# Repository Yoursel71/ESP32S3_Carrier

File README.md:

# ESP32-S3 Carrier Board (KiCad 10)

A 2-layer handheld carrier PCB for the ESP32-S3-DevKitC-1 (N16R8). Every module plugs into 2.54 mm female header sockets; the board itself only carries the sockets, buttons, power circuitry, IR parts and passives.

| | |
|---|---|
| Board | 116 × 200 mm, 2 layers, 1.6 mm FR4, R4 rounded corners, 4× M3 holes (5 mm from the edges) |
| Modules | CC1101 433 MHz (top centre), 2× NRF24L01+PA+LNA, PN532 V3 (I2C), RDM6300 125 kHz, Si5351 clock generator (3× SMA), Catalex microSD, 1.3" SH1106 I2C OLED |
| Power | 18650 Li-ion via JST-PH, TP4056 charger (protected), main power switch, MT3608 boost → 5 V, AMS1117 → 3.3 V, battery level on IO3 |
| On board | 3× IR LED (940 nm) + VS1838B receiver, passive buzzer, 6 buttons (D-pad + OK + BACK), module power switch with soft-start |
| ERC | **0 errors, 0 warnings** (`output/ERC_report.rpt`) |
| DRC | **0 violations, 0 unconnected pads, schematic ↔ PCB in sync** (`--schematic-parity --severity-all`, `output/DRC_report.rpt`) |
| Routing | Freerouting 2.5.0, 100 % routed; GND pour on both layers + 305 stitching vias |
| Tracks | signal 0.25 mm, power 0.6 mm, GND 0.5 mm, minimum 0.20 mm; clearance 0.20–0.25 mm; vias 0.6/0.3 and 0.8/0.4 mm |

## Files

| File | Contents |
|---|---|
| `ESP32S3_Carrier.kicad_pro / .kicad_sch / .kicad_pcb` | KiCad 10 project |
| `Carrier.kicad_sym`, `Carrier.pretty/` | Project symbols and module socket footprints (module body on Fab + courtyard) |
| `output/board_explorer.html` | **Interactive 3D board explorer**: open it in a browser, toggle layers, pull them apart, click a track to light up its whole net and list the connected pins |
| `output/render_top.png`, `render_perspective.png`, `render_bottom.png` | 3D renders |
| `output/assembly_1to1.pdf` | **1:1 assembly check drawing** (A4, unscaled, 50 mm check bar) |
| `output/copper_layers_1to1.pdf` | Top and bottom copper, 1:1 |
| `output/schematic.pdf` | Schematic |
| `output/ERC_report.rpt`, `output/DRC_report.rpt` | Check reports |
| `output/gerbers_ESP32S3_Carrier.zip` | Fabrication files (Gerber + Excellon) |
| `output/BOM.csv` | Bill of materials |
| `scripts/` | Regenerates everything from one source file (`design.py`) |

## Pin map (ESP32-S3)

| Function | GPIO |
|---|---|
| I2C SDA / SCL (OLED 0x3C, PN532 0x24, Si5351 0x60) | IO8 / IO18 (4.7k pull-ups to +3V3_MOD) |
| SPI MOSI / SCK / MISO (CC1101, microSD, 2× NRF24) | IO11 / IO12 / IO13 |
| CC1101 CS / GDO0 / GDO2 | IO10 / IO9 / IO42 |
| microSD CS | IO14 |
| NRF24 #1 CE / CSN / IRQ | IO4 / IO5 / IO21 |
| NRF24 #2 CE / CSN / IRQ | IO6 / IO7 / IO48 |
| IR receiver VS1838B | IO1 |
| IR transmitter (Q1 PN2222A, 220 Ω base, 3 LEDs) | IO2 |
| Passive buzzer (Q2 driver) | IO47 |
| Buttons UP / DOWN / LEFT / RIGHT / OK / BACK (pull to GND) | IO15 / IO16 / IO38 / IO39 / IO40 / IO41 |
| RDM6300 TX (5 V → 3.4 V divider) | IO17 |
| Battery voltage (100k/100k divider, read × 2) | IO3 (ADC) |
| Unused | 0, 19, 20, 35–37, 45, 46, TX/RX, RST |

Enable the internal pull-ups for the buttons. On DevKitC-1 v1.1, IO38 also drives the on-board RGB LED, so the button works but the RGB LED cannot be used at the same time. GDO2 and the two NRF24 IRQ lines are optional; firmware may ignore them.

## Power

```
18650 ─ J10 ─ TP4056 (charges from its own USB, DW01 protection) ─ OUT ─ SW8 main switch (Q4 P-MOSFET)
      ─ MT3608 boost (set to 5.3 V) ─ D5 SS34 ─► +5V
USB → DevKit 5V pin ─────────────────────────────────────────► +5V   (diode-OR'ed with the battery path)

+5V ──[Q3 AO3401A, soft-start]── +5V_MOD ──┬─ microSD (5 V), RDM6300 (5 V), 3× IR LED, buzzer
                     SW7 slide switch drives Q3's gate          └─ U2 AMS1117-3.3 → +3V3_MOD → CC1101, 2× NRF24, PN532, OLED, Si5351, VS1838B
```

- **SW8 (MAIN PWR):** connects the battery to the boost converter. Off = no battery drain (the battery-level divider sits after the switch).
- **Charging:** plug USB into the TP4056 module at the left edge. The protected module's OUT- is the board ground; B- only goes to the cell.
- **Battery + USB together:** the DevKit USB and the boosted battery both feed +5V through diodes, so you can program with the battery connected.
- **Set the MT3608 to 5.3 V** with its trimmer before plugging anything in; after the SS34 drop the rail sits near 4.9 V.
- **SW7 OFF:** the ESP32 keeps running, every module is unpowered.
- **Soft-start:** R16 (100k) + C16 (100 nF gate-drain) ramp +5V_MOD in about 20 ms. Without it, switching ~900 µF of module capacitance on at once would pull the DevKit's 5 V rail down and reset the ESP32.
- The modules' 3.3 V comes from a separate AMS1117, not from the DevKit's 3V3 pin (two PA+LNA radios + PN532 + Wi-Fi would overload the DevKit regulator).
- Decoupling: 100 nF at every module's VCC; an extra 100 µF at the CC1101 and both NRF24s; 470 µF bulk on +3V3_MOD; a 100 µF reservoir next to the IR LEDs.
- Peak current can approach 1 A, so use a decent USB port or charger. Under load +5V_MOD may sit near 4.5 V; if +3V3_MOD sags, replace U2 with a low-dropout SOT-223 regulator that has the same pin-out (1 GND, 2 VOUT, 3 VIN).
- While SW7 is off, firmware should not drive module pins (CS etc.) high, otherwise the modules get back-powered through their I/O pins.

## Rev 1.2

- 18650 battery power: JST-PH battery connector, TP4056 protected charger, main power switch (P-MOSFET), MT3608 5 V boost, SS34 diode-OR with USB.
- Battery voltage measurement on IO3.
- Board grows to 116 × 200 mm; the lower half (DevKit, buttons, Si5351) moved down 30 mm.
- TP4056 and MT3608 are mounted flat and tied to the board with pin legs or short wires (their pad layout varies between clones; check yours against the 1:1 sheet).

## Design review (rev 1.1)

All connections were re-checked pin by pin against the module pin-outs (`scripts/netcheck.py` compares the schematic netlist with `design.py`). Changes from rev 1.0:

1. **Inrush fix (bug):** module power is now soft-started (see above).
2. **IR receiver:** rotated 180° so the lens faces the board edge (it faced inwards); added an R11/C11 (100 Ω / 100 nF) supply filter as recommended in the VS1838B datasheet.
3. **IR transmitter:** three IR LEDs, each with its own 47 Ω resistor (~67 mA each, ~0.2 A total through Q1), plus a 100 µF local reservoir. Drive IO2 only with the modulated 38 kHz carrier and never hold it high: the LEDs and resistors are sized for pulsed use.
4. **SPI chip selects:** 10k pull-ups (R12–R15) keep every SPI device deselected while the ESP32 boots.
5. **CC1101 moved to the centre** of the top edge; the NRF24s sit at the corners with the IR parts in between.
6. **Si5351A added** (7-pin module) on the shared I2C bus, bottom right, with its three SMA outputs over the bottom edge.
7. CC1101 GDO2 and both NRF24 IRQ lines are now routed to free GPIOs.
8. Everything (silkscreen, schematic, files) is in English.

## Dimensions to verify before ordering (IMPORTANT)

The modules are unbranded clones; the footprints use the assumptions below. **Before ordering, print `output/assembly_1to1.pdf` at 100 % / "actual size", check the 50 mm bar with a ruler and lay the modules on the paper.**

> **2×4 sockets (J1 CC1101, J2/J3 NRF24):** a 2×4 header lands in the holes whether it is the right way round, rotated 180° or mirrored, so "the pins fit" proves nothing. Hold the module face up with the SMA pointing away and match the **module's own GND label / square pad** with **GND** on the printout: GND is the bottom-left pin (outer row left to right GND-CE-SCK-MISO, inner row VCC-CSN-MOSI-IRQ). The NRF24 and CC1101 orientation has been confirmed on the real modules.

| Module | Assumed body | Header position (top view) | Source |
|---|---|---|---|
| ESP32-S3-DevKitC-1 | 25.4 × 62.74 mm (+~7 mm antenna overhang) | 2× 1×22, 22.86 mm apart; pin 22 is 8.00 mm from the USB end | Espressif v1.1 dimension drawing (DXF, 2022-04-29), exact |
| CC1101 433 MHz SMA | 27 × 40 mm + SMA | 2×4, centred at the end opposite the SMA; same pin pattern as the NRF24 (GND bottom-left, confirmed) | Owner's ~50×27 mm figure |
| NRF24L01+PA+LNA | 16.5 × 41 mm + SMA | 2×4 centred at the bottom end | Vendor pin-out drawings, confirmed |
| PN532 V3 | 42.7 × 40.4 mm | 1×4 on the left edge, ~6.5 mm in from the edge, vertically centred; 2 diagonal mounting holes | Elechouse V3 manual |
| Si5351A (7-pin) | 30.7 × 21.6 mm + 3 SMA | 1×7 centred on the long edge opposite the SMAs, 2.2 mm from the edge; left to right with the SMAs pointing up: 0, 1, 2, SCL, SDA, GND, VIN (square pad) | Owner's module (CJMCU/Adafruit-style board), confirmed from its drawing |
| OLED 1.3" SH1106 | 35.4 × 33.5 mm | 1×4 centred on the top edge | Typical module size |
| Catalex microSD | 42 × 24 mm | 1×6 on the short edge, card slot at the board edge | Typical module size |
| RDM6300 | 38.5 × 19 mm | P1 along the bottom edge on the right (TX right-most), P2 top left | RDM630 drawing (approximate) |

Tightest gaps between module bodies (plan view): PN532 ↔ DevKit ~1.8 mm, PN532 ↔ C6 ~3.9 mm, PN532 ↔ microSD ~4.1 mm. The PN532 header position was measured from a photo, so check these on paper first.

## Assembly notes

- TP4056 and MT3608: lay the module on its outline and connect each pad hole to the board pad under it with a pin leg or a short wire. Use a protected TP4056 (with DW01 + 8205 MOSFET).
- 18650: use a holder with leads and a 2-pin JST-PH plug; check the polarity (pin 1 = +).
- Female sockets: 2× 1×22, 3× 2×4, 1× 1×7 (Si5351), 2× 1×4 (PN532, OLED), 1× 1×6, 1× 1×5, 1× 1×2 (+ a 1×2 male header for J8). Standard 8.5 mm tall sockets fit.
- Si5351: only SCL, SDA, GND and VIN are used (pins 0/1/2 duplicate the SMA outputs and stay unconnected). VIN is fed from +3V3_MOD on purpose: the module's I2C level shifter pulls the bus up to VIN, so 5 V there would put 5 V on the ESP32's I2C pins.
- Solder straight (not right-angle) male pins to the PN532, pointing down; DIP switch **I2C: 1 = ON, 2 = OFF**. The two holes at its corners are for nylon standoffs.
- The transistors are `PN2222A` (E-B-C). A `P2N2222A` is C-B-E, so check before soldering.
- The IR LEDs use a horizontal footprint and point out of the top edge.
- Keep the 125 kHz coil away from the GND pour and metal (for example on the enclosure lid).
- SMD parts use hand-solder friendly 0805/1206 footprints.

## Regenerating

Needs KiCad 10 (`D:\KiCad`), the Freerouting 2.5.0 jar and Java 25 (paths at the top of `scripts/build.py`).

```
D:\KiCad\bin\python.exe scripts\build.py all       # library → schematic → ERC → PCB → routing → pour → DRC → outputs → 3D explorer
D:\KiCad\bin\python.exe scripts\build.py outputs   # outputs only
```

Change components, nets or positions in `scripts/design.py`; the schematic and the PCB are generated from the same data, so they always match.

After a re-route, DRC may report `starved_thermal` on a GND pad that ends up boxed in by tracks; add that `(ref, pad)` to `SOLID_GND` in `scripts/finish.py` and run `build.py finish` again.

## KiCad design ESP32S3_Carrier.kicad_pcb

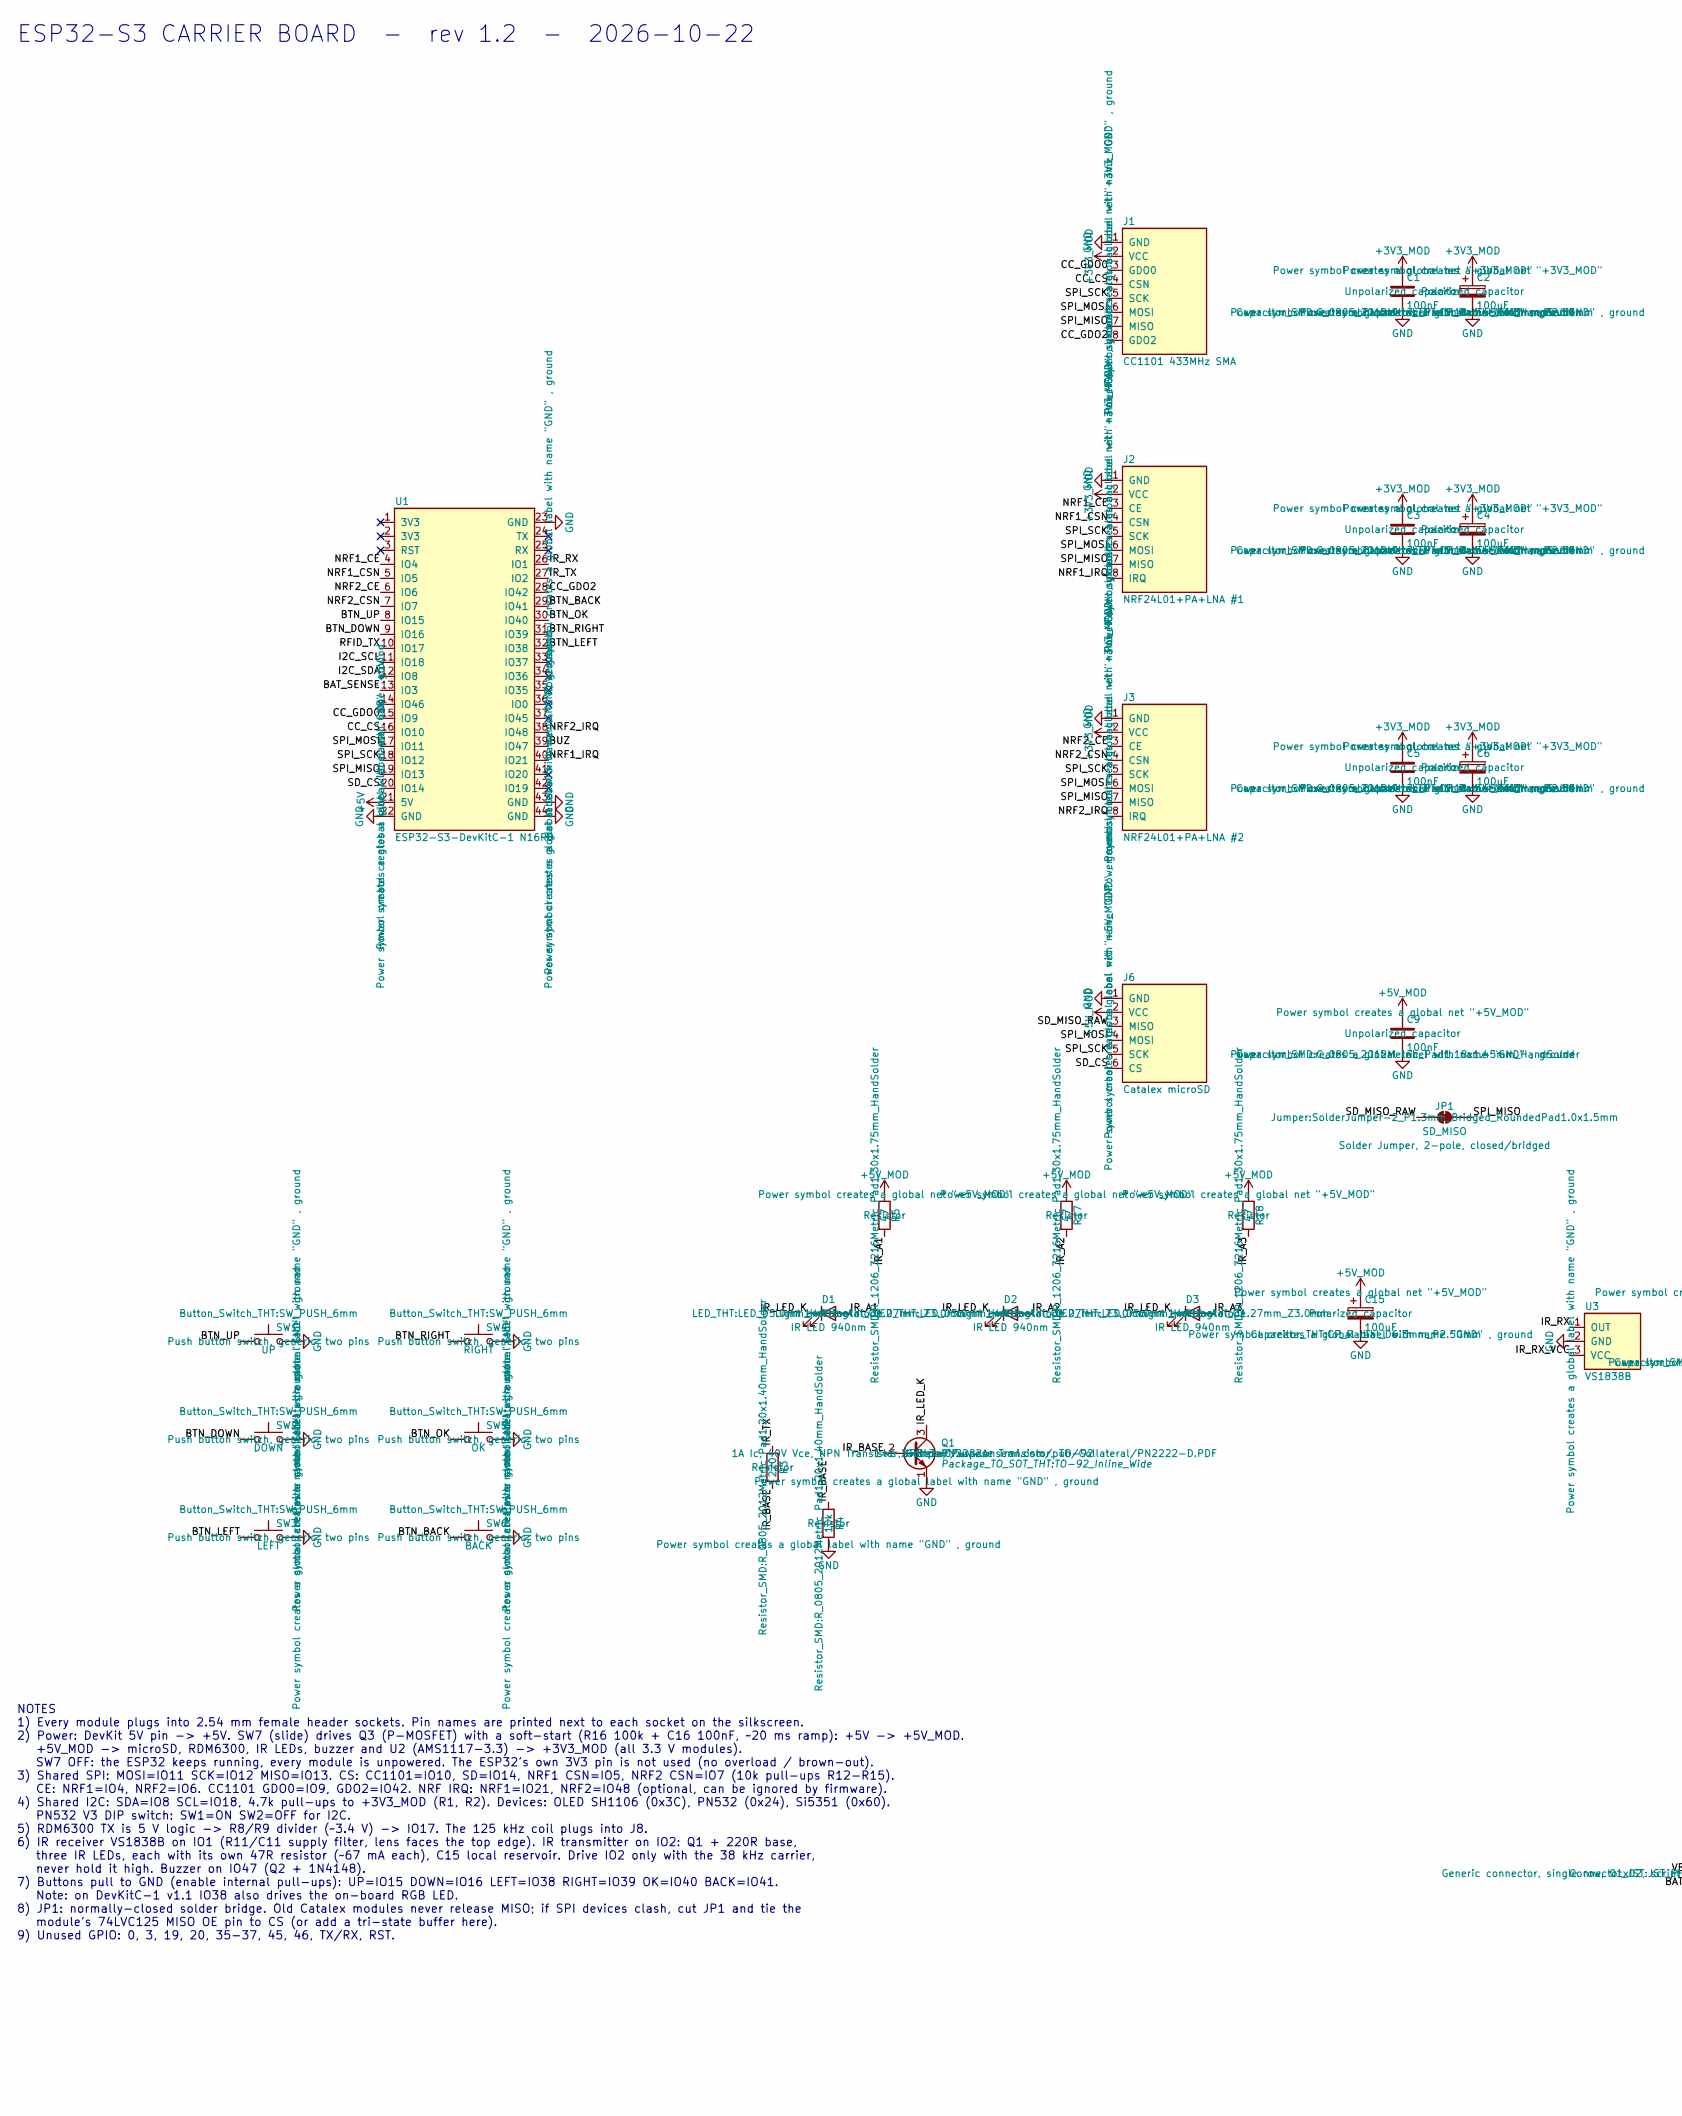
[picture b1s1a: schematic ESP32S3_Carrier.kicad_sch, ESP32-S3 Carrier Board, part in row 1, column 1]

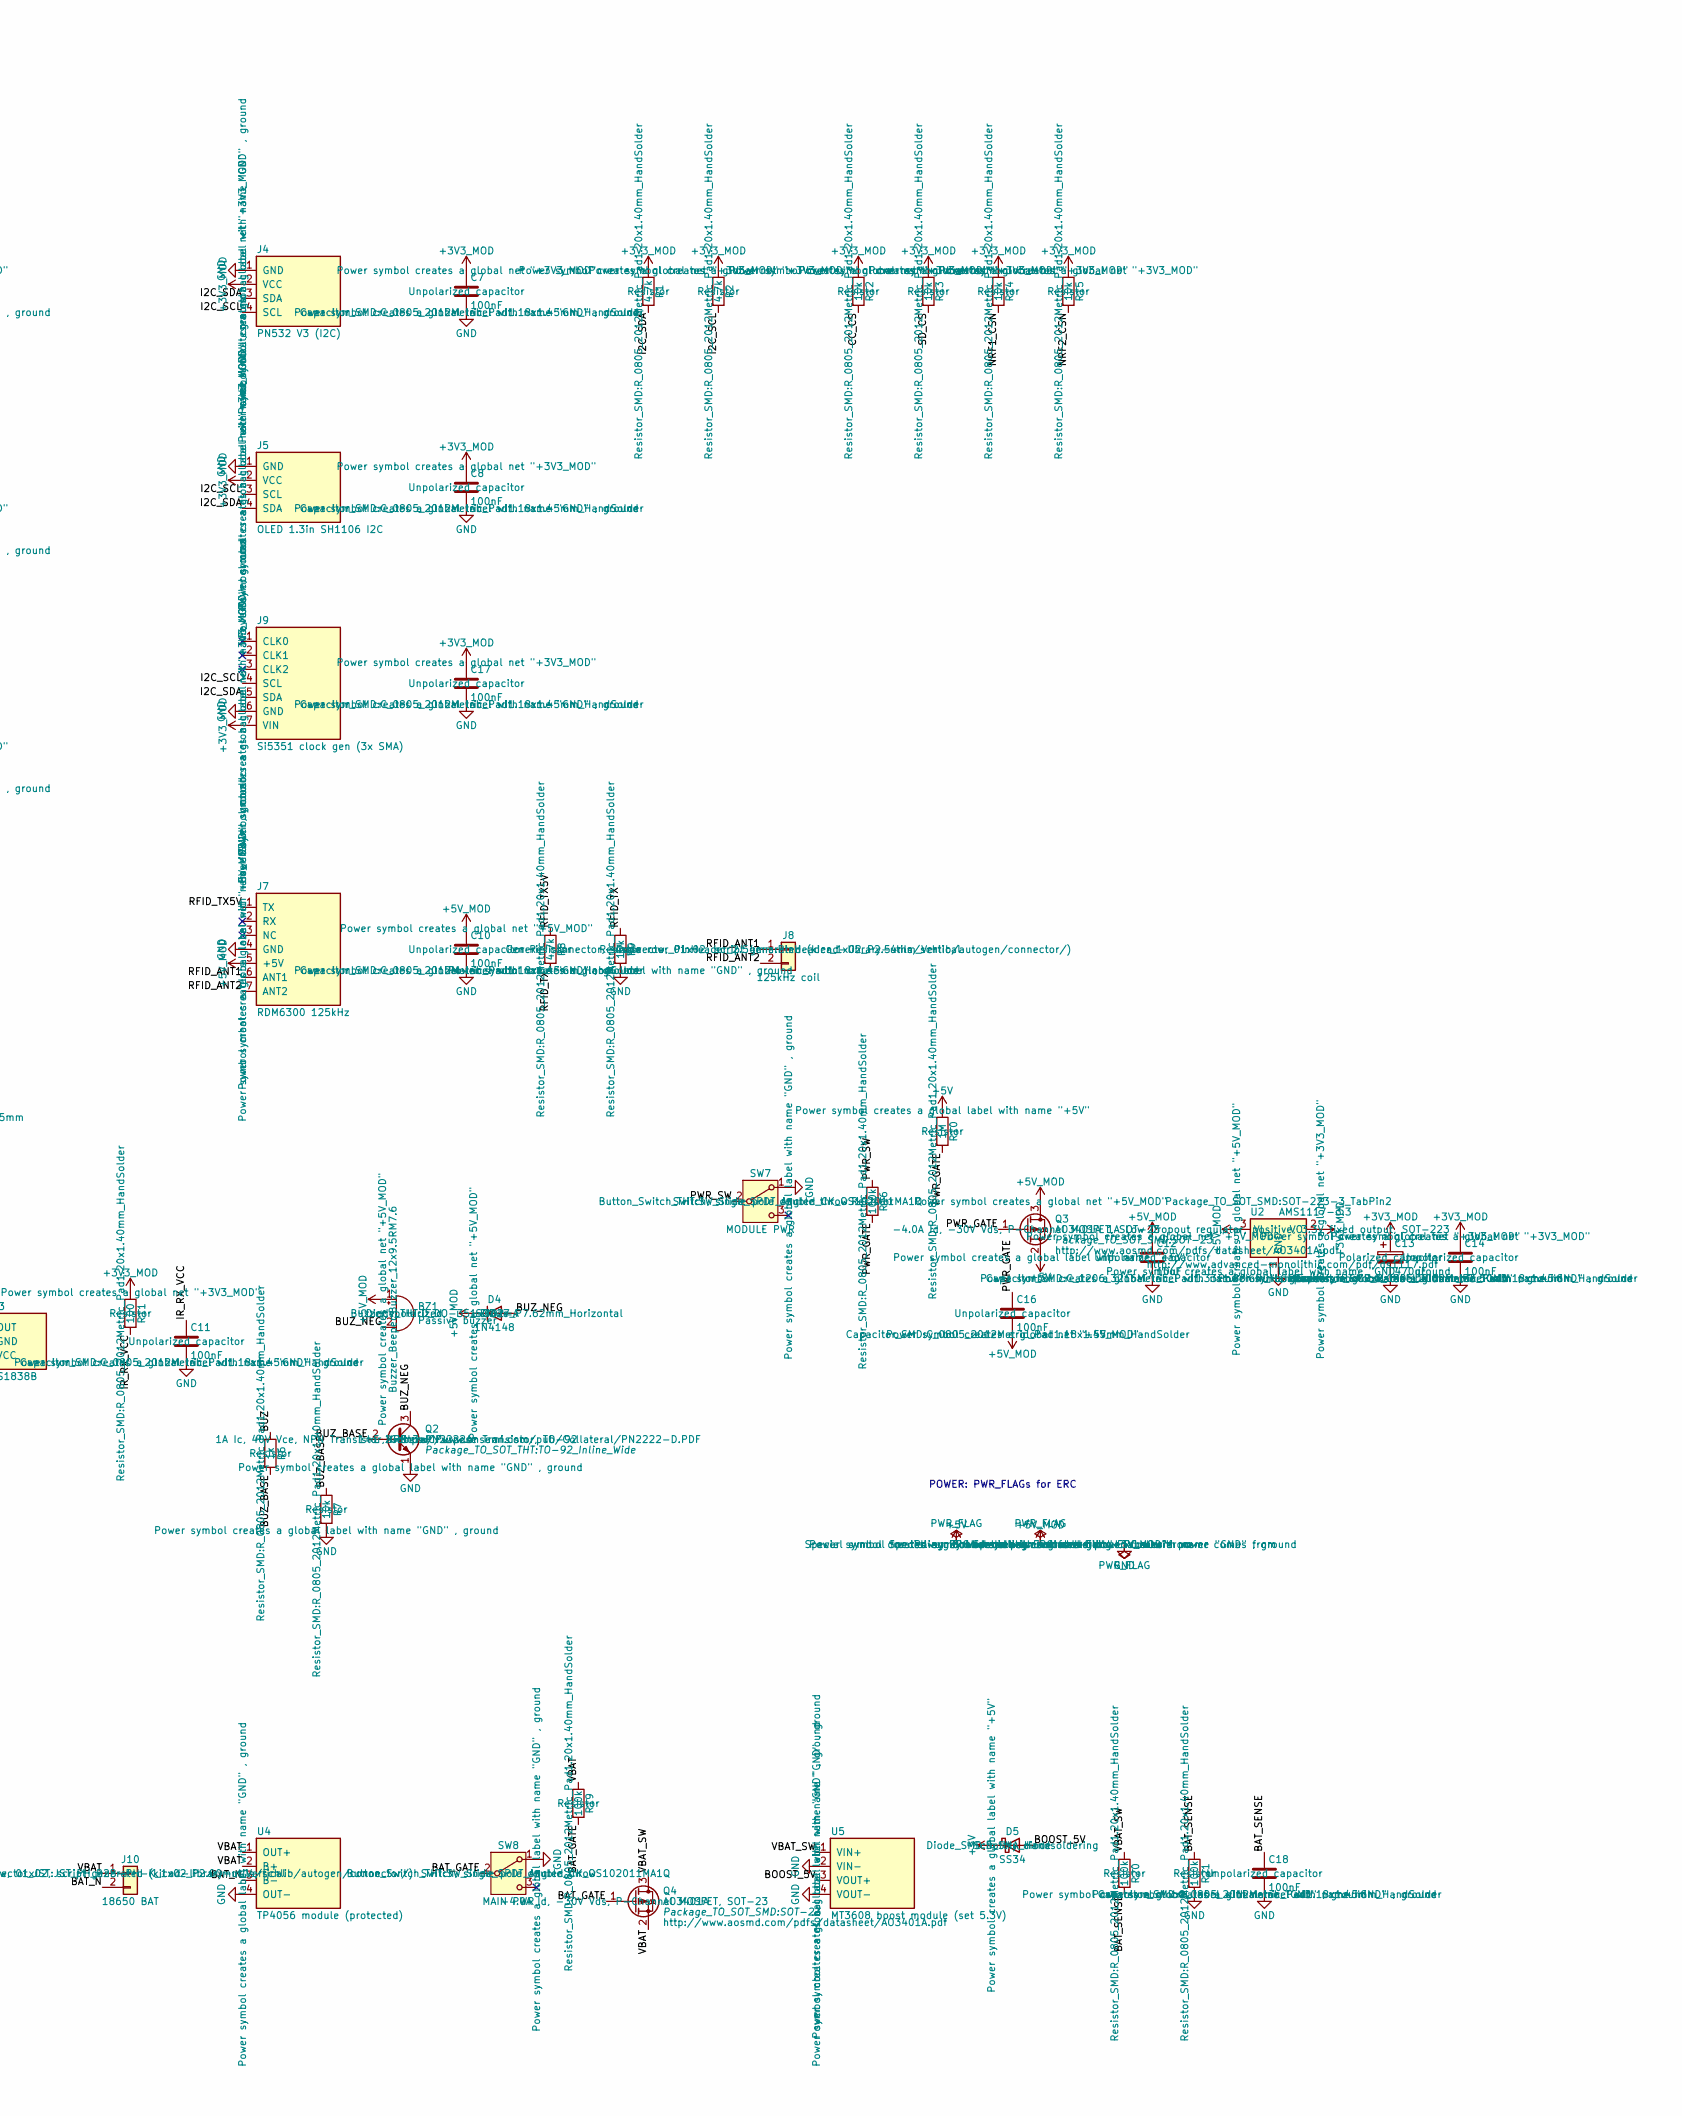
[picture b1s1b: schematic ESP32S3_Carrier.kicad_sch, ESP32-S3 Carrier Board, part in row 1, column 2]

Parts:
BZ1: Passive buzzer; Buzzer_12x9.5RM7.6
C1, C3, C5, C7, C8, C9, C10, C11, C14, C16, C17, C18: 100nF; C_0805_2012Metric_Pad1.18x1.45mm_HandSolder
C2, C4, C6, C15: 100uF; CP_Radial_D6.3mm_P2.50mm
C12: 10uF; C_1206_3216Metric_Pad1.33x1.80mm_HandSolder
C13: 470uF; CP_Radial_D8.0mm_P3.50mm
D1, D2, D3: IR LED 940nm; LED_D5.0mm_Horizontal_O1.27mm_Z3.0mm
D4: 1N4148; D_DO-35_SOD27_P7.62mm_Horizontal
D5: SS34; D_SMA_Handsoldering
J1: CC1101 433MHz SMA; CC1101_SMA_2x4_Socket
J2: NRF24L01+PA+LNA #1; NRF24L01_PA_LNA_Socket
J3: NRF24L01+PA+LNA #2; NRF24L01_PA_LNA_Socket
J4: PN532 V3 (I2C); PN532_V3_I2C_Socket
J5: OLED 1.3in SH1106 I2C; OLED_1.3in_I2C_Socket
J6: Catalex microSD; microSD_Catalex_Socket
J7: RDM6300 125kHz; RDM6300_Socket
J8: 125kHz coil; PinHeader_1x02_P2.54mm_Vertical
J9: Si5351 clock gen (3x SMA); Si5351_3SMA_Socket
J10: 18650 BAT; JST_PH_B2B-PH-K_1x02_P2.00mm_Vertical
JP1: SD_MISO; SolderJumper-2_P1.3mm_Bridged_RoundedPad1.0x1.5mm
Q1, Q2: PN2222A; TO-92_Inline_Wide
Q3, Q4: AO3401A; SOT-23
R1, R2, R8: 4.7k; R_0805_2012Metric_Pad1.20x1.40mm_HandSolder
R3: 220; R_0805_2012Metric_Pad1.20x1.40mm_HandSolder
R4, R7, R9, R12, R13, R14, R15: 10k; R_0805_2012Metric_Pad1.20x1.40mm_HandSolder
R5, R17, R18: 47; R_1206_3216Metric_Pad1.30x1.75mm_HandSolder
R6: 1k; R_0805_2012Metric_Pad1.20x1.40mm_HandSolder
R10: 1M; R_0805_2012Metric_Pad1.20x1.40mm_HandSolder
R11: 100; R_0805_2012Metric_Pad1.20x1.40mm_HandSolder
R16, R19, R20, R21: 100k; R_0805_2012Metric_Pad1.20x1.40mm_HandSolder
SW1: UP; SW_PUSH_6mm
SW2: DOWN; SW_PUSH_6mm
SW3: LEFT; SW_PUSH_6mm
SW4: RIGHT; SW_PUSH_6mm
SW5: OK; SW_PUSH_6mm
SW6: BACK; SW_PUSH_6mm
SW7: MODULE PWR; SW_Slide_SPDT_Angled_CK_OS102011MA1Q
SW8: MAIN PWR; SW_Slide_SPDT_Angled_CK_OS102011MA1Q
U1: ESP32-S3-DevKitC-1 N16R8; ESP32-S3-DevKitC-1_Socket
U2: AMS1117-3.3; SOT-223-3_TabPin2
U3: VS1838B; Vishay_MINICAST-3Pin
U4: TP4056 module (protected); TP4056_Module_Pads
U5: MT3608 boost module (set 5.3V); MT3608_Module_Pads

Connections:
+3V3_MOD: C1.1, C2.1, C3.1, C4.1, C5.1, C6.1, C7.1, C8.1, C13.1, C14.1, C17.1, J1.2 (VCC), J2.2 (VCC), J3.2 (VCC), J4.2 (VCC), J5.2 (VCC), J9.7 (VIN), R1.1, R2.1, R11.1, R12.1, R13.1, R14.1, R15.1, U2.2 (VO)
+5V: D5.1 (K), Q3.2 (S), R10.1, U1.21 (5V)
+5V_MOD: BZ1.1 (+), C9.1, C10.1, C12.1, C15.1, C16.2, D4.1 (K), J6.2 (VCC), J7.5 (+5V), Q3.3 (D), R5.1, R17.1, R18.1, U2.3 (VI)
/BAT_GATE: Q4.1 (G), R19.2, SW8.2 (B)
/BAT_N: J10.2, U4.3 (B-)
/BAT_SENSE: C18.1, R20.2, R21.1, U1.13 (IO3)
/BOOST_5V: D5.2 (A), U5.3 (VOUT+)
/BTN_BACK: SW6.1, U1.29 (IO41)
/BTN_DOWN: SW2.1, U1.9 (IO16)
/BTN_LEFT: SW3.1, U1.32 (IO38)
/BTN_OK: SW5.1, U1.30 (IO40)
/BTN_RIGHT: SW4.1, U1.31 (IO39)
/BTN_UP: SW1.1, U1.8 (IO15)
/BUZ: R6.1, U1.39 (IO47)
/BUZ_BASE: Q2.2 (B), R6.2, R7.1
/BUZ_NEG: BZ1.2 (-), D4.2 (A), Q2.3 (C)
/CC_CS: J1.4 (CSN), R12.2, U1.16 (IO10)
/CC_GDO0: J1.3 (GDO0), U1.15 (IO9)
/CC_GDO2: J1.8 (GDO2), U1.28 (IO42)
/I2C_SCL: J4.4 (SCL), J5.3 (SCL), J9.4 (SCL), R2.2, U1.11 (IO18)
/I2C_SDA: J4.3 (SDA), J5.4 (SDA), J9.5 (SDA), R1.2, U1.12 (IO8)
/IR_A1: D1.2 (A), R5.2
/IR_A2: D2.2 (A), R17.2
/IR_A3: D3.2 (A), R18.2
/IR_BASE: Q1.2 (B), R3.2, R4.1
/IR_LED_K: D1.1 (K), D2.1 (K), D3.1 (K), Q1.3 (C)
/IR_RX: U1.26 (IO1), U3.1 (OUT)
/IR_RX_VCC: C11.1, R11.2, U3.3 (VCC)
/IR_TX: R3.1, U1.27 (IO2)
/NRF1_CE: J2.3 (CE), U1.4 (IO4)
/NRF1_CSN: J2.4 (CSN), R14.2, U1.5 (IO5)
/NRF1_IRQ: J2.8 (IRQ), U1.40 (IO21)
/NRF2_CE: J3.3 (CE), U1.6 (IO6)
/NRF2_CSN: J3.4 (CSN), R15.2, U1.7 (IO7)
/NRF2_IRQ: J3.8 (IRQ), U1.38 (IO48)
/PWR_GATE: C16.1, Q3.1 (G), R10.2, R16.2
/PWR_SW: R16.1, SW7.2 (B)
/RFID_ANT1: J7.6 (ANT1), J8.1
/RFID_ANT2: J7.7 (ANT2), J8.2
/RFID_TX: R8.2, R9.1, U1.10 (IO17)
/RFID_TX5V: J7.1 (TX), R8.1
/SD_CS: J6.6 (CS), R13.2, U1.20 (IO14)
/SD_MISO_RAW: J6.3 (MISO), JP1.1 (A)
/SPI_MISO: J1.7 (MISO), J2.7 (MISO), J3.7 (MISO), JP1.2 (B), U1.19 (IO13)
/SPI_MOSI: J1.6 (MOSI), J2.6 (MOSI), J3.6 (MOSI), J6.4 (MOSI), U1.17 (IO11)
/SPI_SCK: J1.5 (SCK), J2.5 (SCK), J3.5 (SCK), J6.5 (SCK), U1.18 (IO12)
/VBAT: J10.1, Q4.2 (S), R19.1, U4.1 (OUT+), U4.2 (B+)
/VBAT_SW: Q4.3 (D), R20.1, U5.1 (VIN+)
GND: C1.2, C2.2, C3.2, C4.2, C5.2, C6.2, C7.2, C8.2, C9.2, C10.2, C11.2, C12.2, C13.2, C14.2, C15.2, C17.2, C18.2, J1.1 (GND), J2.1 (GND), J3.1 (GND), J4.1 (GND), J5.1 (GND), J6.1 (GND), J7.4 (GND), J9.6 (GND), Q1.1 (E), Q2.1 (E), R4.2, R7.2, R9.2, R21.2, SW1.2, SW2.2, SW3.2, SW4.2, SW5.2, SW6.2, SW7.1 (A), SW8.1 (A), U1.22 (GND), U1.23 (GND), U1.43 (GND), U1.44 (GND), U2.1 (GND), U3.2 (GND), U4.4 (OUT-), U5.2 (VIN-), U5.4 (VOUT-)

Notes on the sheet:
ESP32-S3 CARRIER BOARD - rev 1.2 - 2026-10-22
NOTES 1) Every module plugs into 2.54 mm female header sockets. Pin names are printed next to each socket on the silkscreen. 2) Power: DevKit 5V pin -> +5V. SW7 (slide) drives Q3 (P-MOSFET) with a soft-start (R16 100k + C16 100nF, ~20 ms ramp): +5V -> +5V_MOD. +5V_MOD -> microSD, RDM6300, IR LEDs, 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
POWER: PWR_FLAGs for ERC

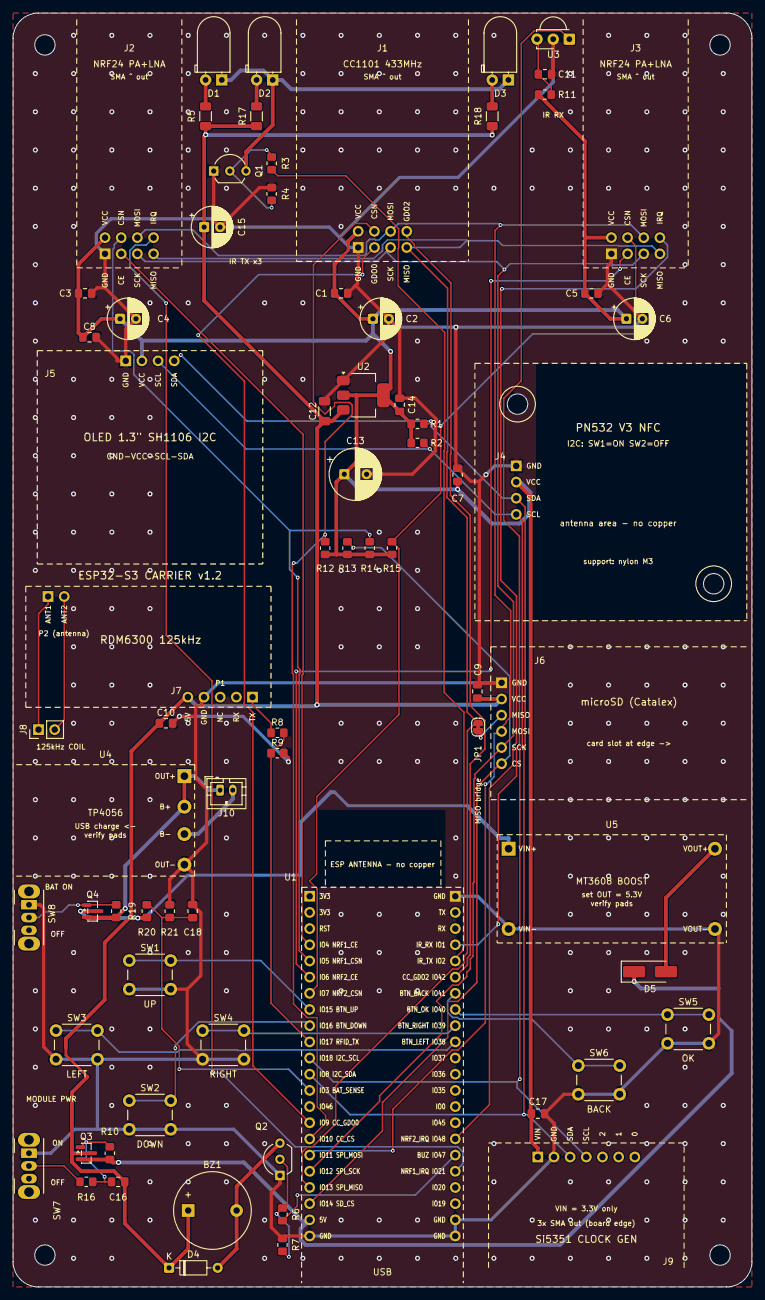
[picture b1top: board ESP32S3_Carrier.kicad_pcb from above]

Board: 2 copper layers, 116.0 x 200.0 mm, 77 parts (0 on the bottom side), 49 nets.

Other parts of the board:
H1, H2, H3, H4: M3; MountingHole_3.2mm_M3

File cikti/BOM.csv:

"Referans","Deger","Footprint","Adet"
"BZ1","Pasif buzzer","Buzzer_Beeper:Buzzer_12x9.5RM7.6","1"
"C1,C3,C5,C7,C8,C9,C10,C11,C14","100nF","Capacitor_SMD:C_0805_2012Metric_Pad1.18x1.45mm_HandSolder","9"
"C2,C4,C6","100uF","Capacitor_THT:CP_Radial_D6.3mm_P2.50mm","3"
"C12","10uF","Capacitor_SMD:C_1206_3216Metric_Pad1.33x1.80mm_HandSolder","1"
"C13","470uF","Capacitor_THT:CP_Radial_D8.0mm_P3.50mm","1"
"D1","IR LED 940nm","LED_THT:LED_D5.0mm_Horizontal_O1.27mm_Z3.0mm","1"
"D2","1N4148","Diode_THT:D_DO-35_SOD27_P7.62mm_Horizontal","1"
"J1","CC1101 433MHz SMA","Tasiyici:CC1101_SMA_2x4_Soket","1"
"J2","NRF24L01+PA+LNA #1","Tasiyici:NRF24L01_PA_LNA_Soket","1"
"J3","NRF24L01+PA+LNA #2","Tasiyici:NRF24L01_PA_LNA_Soket","1"
"J4","PN532 V3 (I2C)","Tasiyici:PN532_V3_I2C_Soket","1"
"J5","OLED 1.3in SH1106 I2C","Tasiyici:OLED_1.3in_I2C_Soket","1"
"J6","Catalex microSD","Tasiyici:microSD_Catalex_Soket","1"
"J7","RDM6300 125kHz","Tasiyici:RDM6300_Soket","1"
"J8","125kHz bobin","Connector_PinHeader_2.54mm:PinHeader_1x02_P2.54mm_Vertical","1"
"Q1,Q2","PN2222A","Package_TO_SOT_THT:TO-92_Inline_Wide","2"
"Q3","AO3401A","Package_TO_SOT_SMD:SOT-23","1"
"R1,R2,R8","4.7k","Resistor_SMD:R_0805_2012Metric_Pad1.20x1.40mm_HandSolder","3"
"R3","220","Resistor_SMD:R_0805_2012Metric_Pad1.20x1.40mm_HandSolder","1"
"R4,R7,R9","10k","Resistor_SMD:R_0805_2012Metric_Pad1.20x1.40mm_HandSolder","3"
"R5","47","Resistor_SMD:R_1206_3216Metric_Pad1.30x1.75mm_HandSolder","1"
"R6","1k","Resistor_SMD:R_0805_2012Metric_Pad1.20x1.40mm_HandSolder","1"
"R10","100k","Resistor_SMD:R_0805_2012Metric_Pad1.20x1.40mm_HandSolder","1"
"SW1","UP","Button_Switch_THT:SW_PUSH_6mm","1"
"SW2","DOWN","Button_Switch_THT:SW_PUSH_6mm","1"
"SW3","LEFT","Button_Switch_THT:SW_PUSH_6mm","1"
"SW4","RIGHT","Button_Switch_THT:SW_PUSH_6mm","1"
"SW5","OK","Button_Switch_THT:SW_PUSH_6mm","1"
"SW6","BACK","Button_Switch_THT:SW_PUSH_6mm","1"
"SW7","MODUL GUC","Button_Switch_THT:SW_Slide_SPDT_Angled_CK_OS102011MA1Q","1"
"U1","ESP32-S3-DevKitC-1 N16R8","Tasiyici:ESP32-S3-DevKitC-1_Soket","1"
"U2","AMS1117-3.3","Package_TO_SOT_SMD:SOT-223-3_TabPin2","1"
"U3","VS1838B","OptoDevice:Vishay_MINICAST-3Pin","1"

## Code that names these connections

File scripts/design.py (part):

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    dict(ref="U1", val="ESP32-S3-DevKitC-1 N16R8", sym="Carrier:ESP32-S3-DevKitC-1",
         fp="Carrier:ESP32-S3-DevKitC-1_Socket", pins=devkit_pins(), sch=(101.6, 132.08), pcb=(46.57, 138.66, 0)),
    dict(ref="J1", val="CC1101 433MHz SMA", sym="Carrier:CC1101_SMA_2x4", fp="Carrier:CC1101_SMA_2x4_Socket",
         pins={"1": "GND", "2": "+3V3_MOD", "3": "CC_GDO0", "4": "CC_CS", "5": "SPI_SCK", "6": "SPI_MOSI",
               "7": "SPI_MISO", "8": "CC_GDO2"}, sch=(228.6, 63.5), pcb=(54.19, 36.8, 0)),
    dict(ref="J2", val="NRF24L01+PA+LNA #1", sym="Carrier:NRF24L01_PA_LNA", fp="Carrier:NRF24L01_PA_LNA_Socket",
         pins={"1": "GND", "2": "+3V3_MOD", "3": "NRF1_CE", "4": "NRF1_CSN", "5": "SPI_SCK", "6": "SPI_MOSI",
               "7": "SPI_MISO", "8": "NRF1_IRQ"}, sch=(228.6, 106.68), pcb=(14.44, 37.8, 0)),
    dict(ref="J3", val="NRF24L01+PA+LNA #2", sym="Carrier:NRF24L01_PA_LNA", fp="Carrier:NRF24L01_PA_LNA_Socket",
         pins={"1": "GND", "2": "+3V3_MOD", "3": "NRF2_CE", "4": "NRF2_CSN", "5": "SPI_SCK", "6": "SPI_MOSI",
               "7": "SPI_MISO", "8": "NRF2_IRQ"}, sch=(228.6, 149.86), pcb=(93.94, 37.8, 0)),
    dict(ref="J4", val="PN532 V3 (I2C)", sym="Carrier:PN532_I2C", fp="Carrier:PN532_V3_I2C_Socket",
         pins={"1": "GND", "2": "+3V3_MOD", "3": "I2C_SDA", "4": "I2C_SCL"}, sch=(360.68, 63.5), pcb=(79.0, 71.09, 0)),
    dict(ref="J5", val="OLED 1.3in SH1106 I2C", sym="Carrier:OLED_SH1106_I2C", fp="Carrier:OLED_1.3in_I2C_Socket",
         pins={"1": "GND", "2": "+3V3_MOD", "3": "I2C_SCL", "4": "I2C_SDA"}, sch=(360.68, 99.06), pcb=(17.69, 54.6, 0)),
    dict(ref="J6", val="Catalex microSD", sym="Carrier:microSD_Catalex", fp="Carrier:microSD_Catalex_Socket",
         pins={"1": "GND", "2": "+5V_MOD", "3": "SD_MISO_RAW", "4": "SPI_MOSI", "5": "SPI_SCK", "6": "SD_CS"},
         sch=(228.6, 198.12), pcb=(76.7, 105.15, 0)),
    dict(ref="J7", val="RDM6300 125kHz", sym="Carrier:RDM6300", fp="Carrier:RDM6300_Socket",
         pins={"1": "RFID_TX5V", "2": None, "3": None, "4": "GND", "5": "+5V_MOD", "6": "RFID_ANT1", "7": "RFID_ANT2"},
         sch=(360.68, 182.88), pcb=(37.6, 107.4, 0)),
    dict(ref="J8", val="125kHz coil", sym="Connector_Generic:Conn_01x02",
         fp="Connector_PinHeader_2.54mm:PinHeader_1x02_P2.54mm_Vertical",
         pins={"1": "RFID_ANT1", "2": "RFID_ANT2"}, sch=(449.58, 182.88), pcb=(4.0, 112.5, 90)),
    dict(ref="J9", val="Si5351 clock gen (3x SMA)", sym="Carrier:Si5351_7pin", fp="Carrier:Si5351_3SMA_Socket",
         pins={"1": None, "2": None, "3": None, "4": "I2C_SCL", "5": "I2C_SDA", "6": "GND", "7": "+3V3_MOD"},
         sch=(360.68, 134.62), pcb=(97.62, 179.6, 180)),

    # --- Decoupling ---
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    # --- microSD MISO cuttable bridge ---
    dict(ref="JP1", val="SD_MISO", sym="Jumper:SolderJumper_2_Bridged",
         fp="Jumper:SolderJumper-2_P1.3mm_Bridged_RoundedPad1.0x1.5mm",
         pins={"1": "SD_MISO_RAW", "2": "SPI_MISO"}, sch=(279.4, 213.36), pcb=(73.0, 112.1, 90)),

    # --- RDM6300 TX 5V -> 3.4V divider ---
    R("R8", "4.7k", R0805, "RFID_TX5V", "RFID_TX", (406.4, 182.88), (41.5, 113.0, 0)),
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    R("R17", "47", R1206, "+5V_MOD", "IR_A2", (210.82, 231.14), (38.23, 16.2, 90)),
    R("R18", "47", R1206, "+5V_MOD", "IR_A3", (243.84, 231.14), (75.23, 16.2, 90)),
    dict(ref="Q1", val="PN2222A", sym="Carrier:PN2222A", fp=TO92,
         pins={"1": "GND", "2": "IR_BASE", "3": "IR_LED_K"}, sch=(182.88, 274.32), pcb=(31.5, 24.8, 0)),
    R("R3", "220", R0805, "IR_TX", "IR_BASE", (157.48, 276.86), (40.6, 23.6, 90)),
    R("R4", "10k", R0805, "IR_BASE", "GND", (167.64, 287.02), (40.6, 28.4, 90)),
    CP("C15", "100uF", CP63, "+5V_MOD", "GND", (264.16, 248.92), (30.0, 33.6, 0)),

    # --- IR receiver (lens faces the top edge) + RC supply filter ---
    dict(ref="U3", val="VS1838B", sym="Carrier:VS1838B", fp="OptoDevice:Vishay_MINICAST-3Pin",
         pins={"1": "IR_RX", "2": "GND", "3": "IR_RX_VCC"}, sch=(309.88, 254.0), pcb=(87.34, 4.1, 180)),
    R("R11", "100", R0805, "+3V3_MOD", "IR_RX_VCC", (330.2, 248.92), (83.5, 12.8, 0)),

    # --- Buzzer driver ---
    dict(ref="BZ1", val="Passive buzzer", sym="Device:Buzzer", fp="Buzzer_Beeper:Buzzer_12x9.5RM7.6",
         pins={"1": "+5V_MOD", "2": "BUZ_NEG"}, sch=(378.46, 248.92), pcb=(27.5, 188.0, 0)),
    dict(ref="D4", val="1N4148", sym="Device:D", fp="Diode_THT:D_DO-35_SOD27_P7.62mm_Horizontal",
         pins={"1": "+5V_MOD", "2": "BUZ_NEG"}, sch=(396.24, 248.92), pcb=(24.5, 197.0, 0)),
    dict(ref="Q2", val="PN2222A", sym="Carrier:PN2222A", fp=TO92,
         pins={"1": "GND", "2": "BUZ_BASE", "3": "BUZ_NEG"}, sch=(378.46, 271.78), pcb=(41.9, 182.5, 90)),
    R("R6", "1k", R0805, "BUZ", "BUZ_BASE", (355.6, 274.32), (42.3, 188.6, 90)),
    R("R7", "10k", R0805, "BUZ_BASE", "GND", (365.76, 284.48), (42.3, 193.4, 90)),

    # --- Module power switch (soft-start P-MOSFET) + 3.3 V regulator ---
    dict(ref="SW7", val="MODULE PWR", sym="Switch:SW_SPDT", fp="Button_Switch_THT:SW_Slide_SPDT_Angled_CK_OS102011MA1Q",
         pins={"1": "GND", "2": "PWR_SW", "3": None}, sch=(444.5, 228.6), pcb=(2.5, 179.0, 270)),
    R("R16", "100k", R0805, "PWR_SW", "PWR_GATE", (464.82, 228.6), (11.5, 183.5, 0)),
    R("R10", "1M", R0805, "+5V", "PWR_GATE", (477.52, 215.9), (15.2, 179.0, 90)),
    C("C16", "100nF", C0805, "PWR_GATE", "+5V_MOD", (490.22, 248.92), (16.5, 183.5, 0)),
    dict(ref="Q3", val="AO3401A", sym="Carrier:AO3401A", fp="Package_TO_SOT_SMD:SOT-23",
         pins={"1": "PWR_GATE", "2": "+5V", "3": "+5V_MOD"}, sch=(492.76, 233.68), pcb=(11.5, 179.0, 0)),
    dict(ref="U2", val="AMS1117-3.3", sym="Carrier:AMS1117-3.3", fp="Package_TO_SOT_SMD:SOT-223-3_TabPin2",
         pins={"1": "GND", "2": "+3V3_MOD", "3": "+5V_MOD"}, sch=(538.48, 233.68), pcb=(55.0, 60.0, 0)),
    C("C12", "10uF", C1206, "+5V_MOD", "GND", (515.62, 238.76), (48.9, 62.5, 90)),
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    # --- Battery: 18650 -> TP4056 (charge + protection) -> main switch -> MT3608 boost -> SS34 -> +5V ---
    dict(ref="J10", val="18650 BAT", sym="Connector_Generic:Conn_01x02",
         fp="Connector_JST:JST_PH_B2B-PH-K_1x02_P2.00mm_Vertical",
         pins={"1": "VBAT", "2": "BAT_N"}, sch=(330.2, 350.52), pcb=(32.5, 122.0, 0)),
    dict(ref="U4", val="TP4056 module (protected)", sym="Carrier:TP4056_Module", fp="Carrier:TP4056_Module_Pads",
         pins={"1": "VBAT", "2": "VBAT", "3": "BAT_N", "4": "GND"}, sch=(360.68, 350.52), pcb=(0.5, 118.0, 0)),
    dict(ref="SW8", val="MAIN PWR", sym="Switch:SW_SPDT", fp="Button_Switch_THT:SW_Slide_SPDT_Angled_CK_OS102011MA1Q",
         pins={"1": "GND", "2": "BAT_GATE", "3": None}, sch=(398.78, 350.52), pcb=(2.5, 140.0, 270)),
    R("R19", "100k", R0805, "VBAT", "BAT_GATE", (411.48, 337.82), (16.2, 141.0, 90)),
    dict(ref="Q4", val="AO3401A", sym="Carrier:AO3401A", fp="Package_TO_SOT_SMD:SOT-23",
         pins={"1": "BAT_GATE", "2": "VBAT", "3": "VBAT_SW"}, sch=(421.64, 355.6), pcb=(12.5, 141.0, 0)),
    dict(ref="U5", val="MT3608 boost module (set 5.3V)", sym="Carrier:MT3608_Module", fp="Carrier:MT3608_Module_Pads",
         pins={"1": "VBAT_SW", "2": "GND", "3": "BOOST_5V", "4": "GND"}, sch=(464.82, 350.52), pcb=(76.0, 129.0, 0)),
    dict(ref="D5", val="SS34", sym="Device:D_Schottky", fp="Diode_SMD:D_SMA_Handsoldering",
         pins={"1": "+5V", "2": "BOOST_5V"}, sch=(490.22, 345.44), pcb=(100.0, 150.5, 0)),
    R("R20", "100k", R0805, "VBAT_SW", "BAT_SENSE", (510.54, 350.52), (21.0, 141.0, 90)),
    R("R21", "100k", R0805, "BAT_SENSE", "GND", (523.24, 350.52), (24.6, 141.0, 90)),
    C("C18", "100nF", C0805, "BAT_SENSE", "GND", (535.94, 350.52), (28.2, 141.0, 90)),
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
